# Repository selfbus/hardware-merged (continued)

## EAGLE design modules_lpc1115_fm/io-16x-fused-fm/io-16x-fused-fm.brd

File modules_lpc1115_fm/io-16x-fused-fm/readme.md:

<h1>Module with 16 fused IOs (flush mount) with I2C and SPI</h1>

The unversioned *.sch and *.brd files are the development files. 
Once a new version is released, a corresponding copy of the files with the release version appended to the file name are provided. 

Project documentation: https://selfbus.org/wiki/devices/inputs/82-multifunktions-io-modul-16x-fused-io-spi-i2c-serial</br>
Forum discussions: https://selfbus.org/forum/app.php/tag/Eingangsmodul

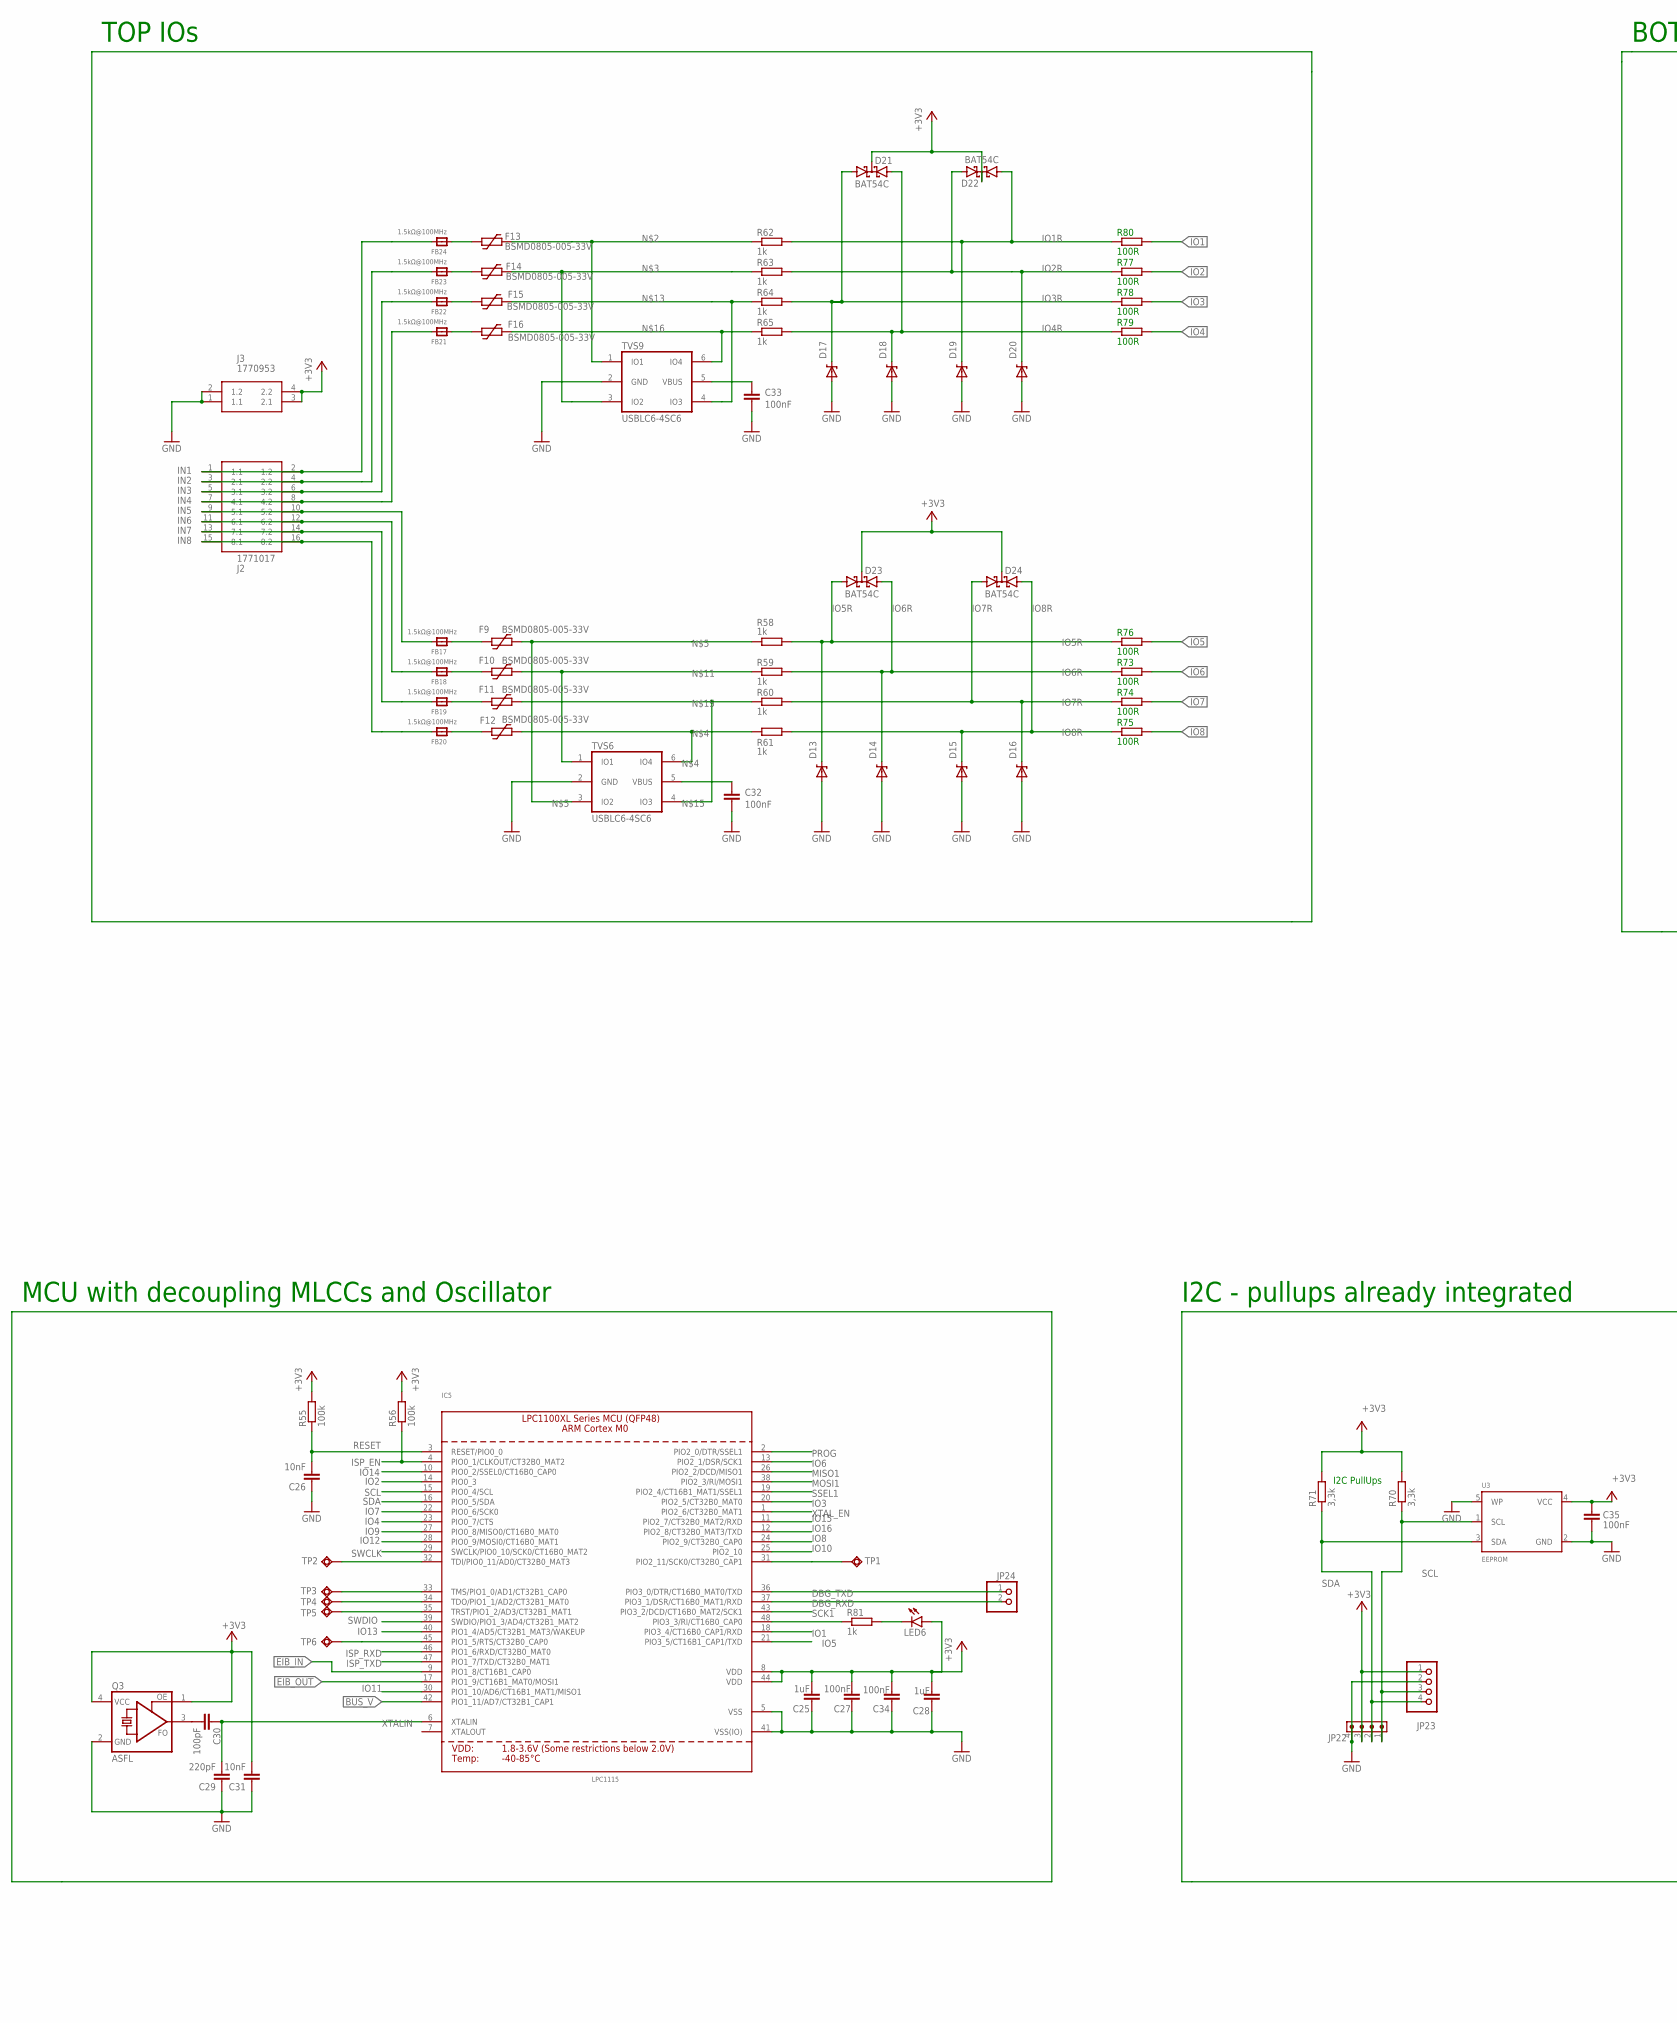
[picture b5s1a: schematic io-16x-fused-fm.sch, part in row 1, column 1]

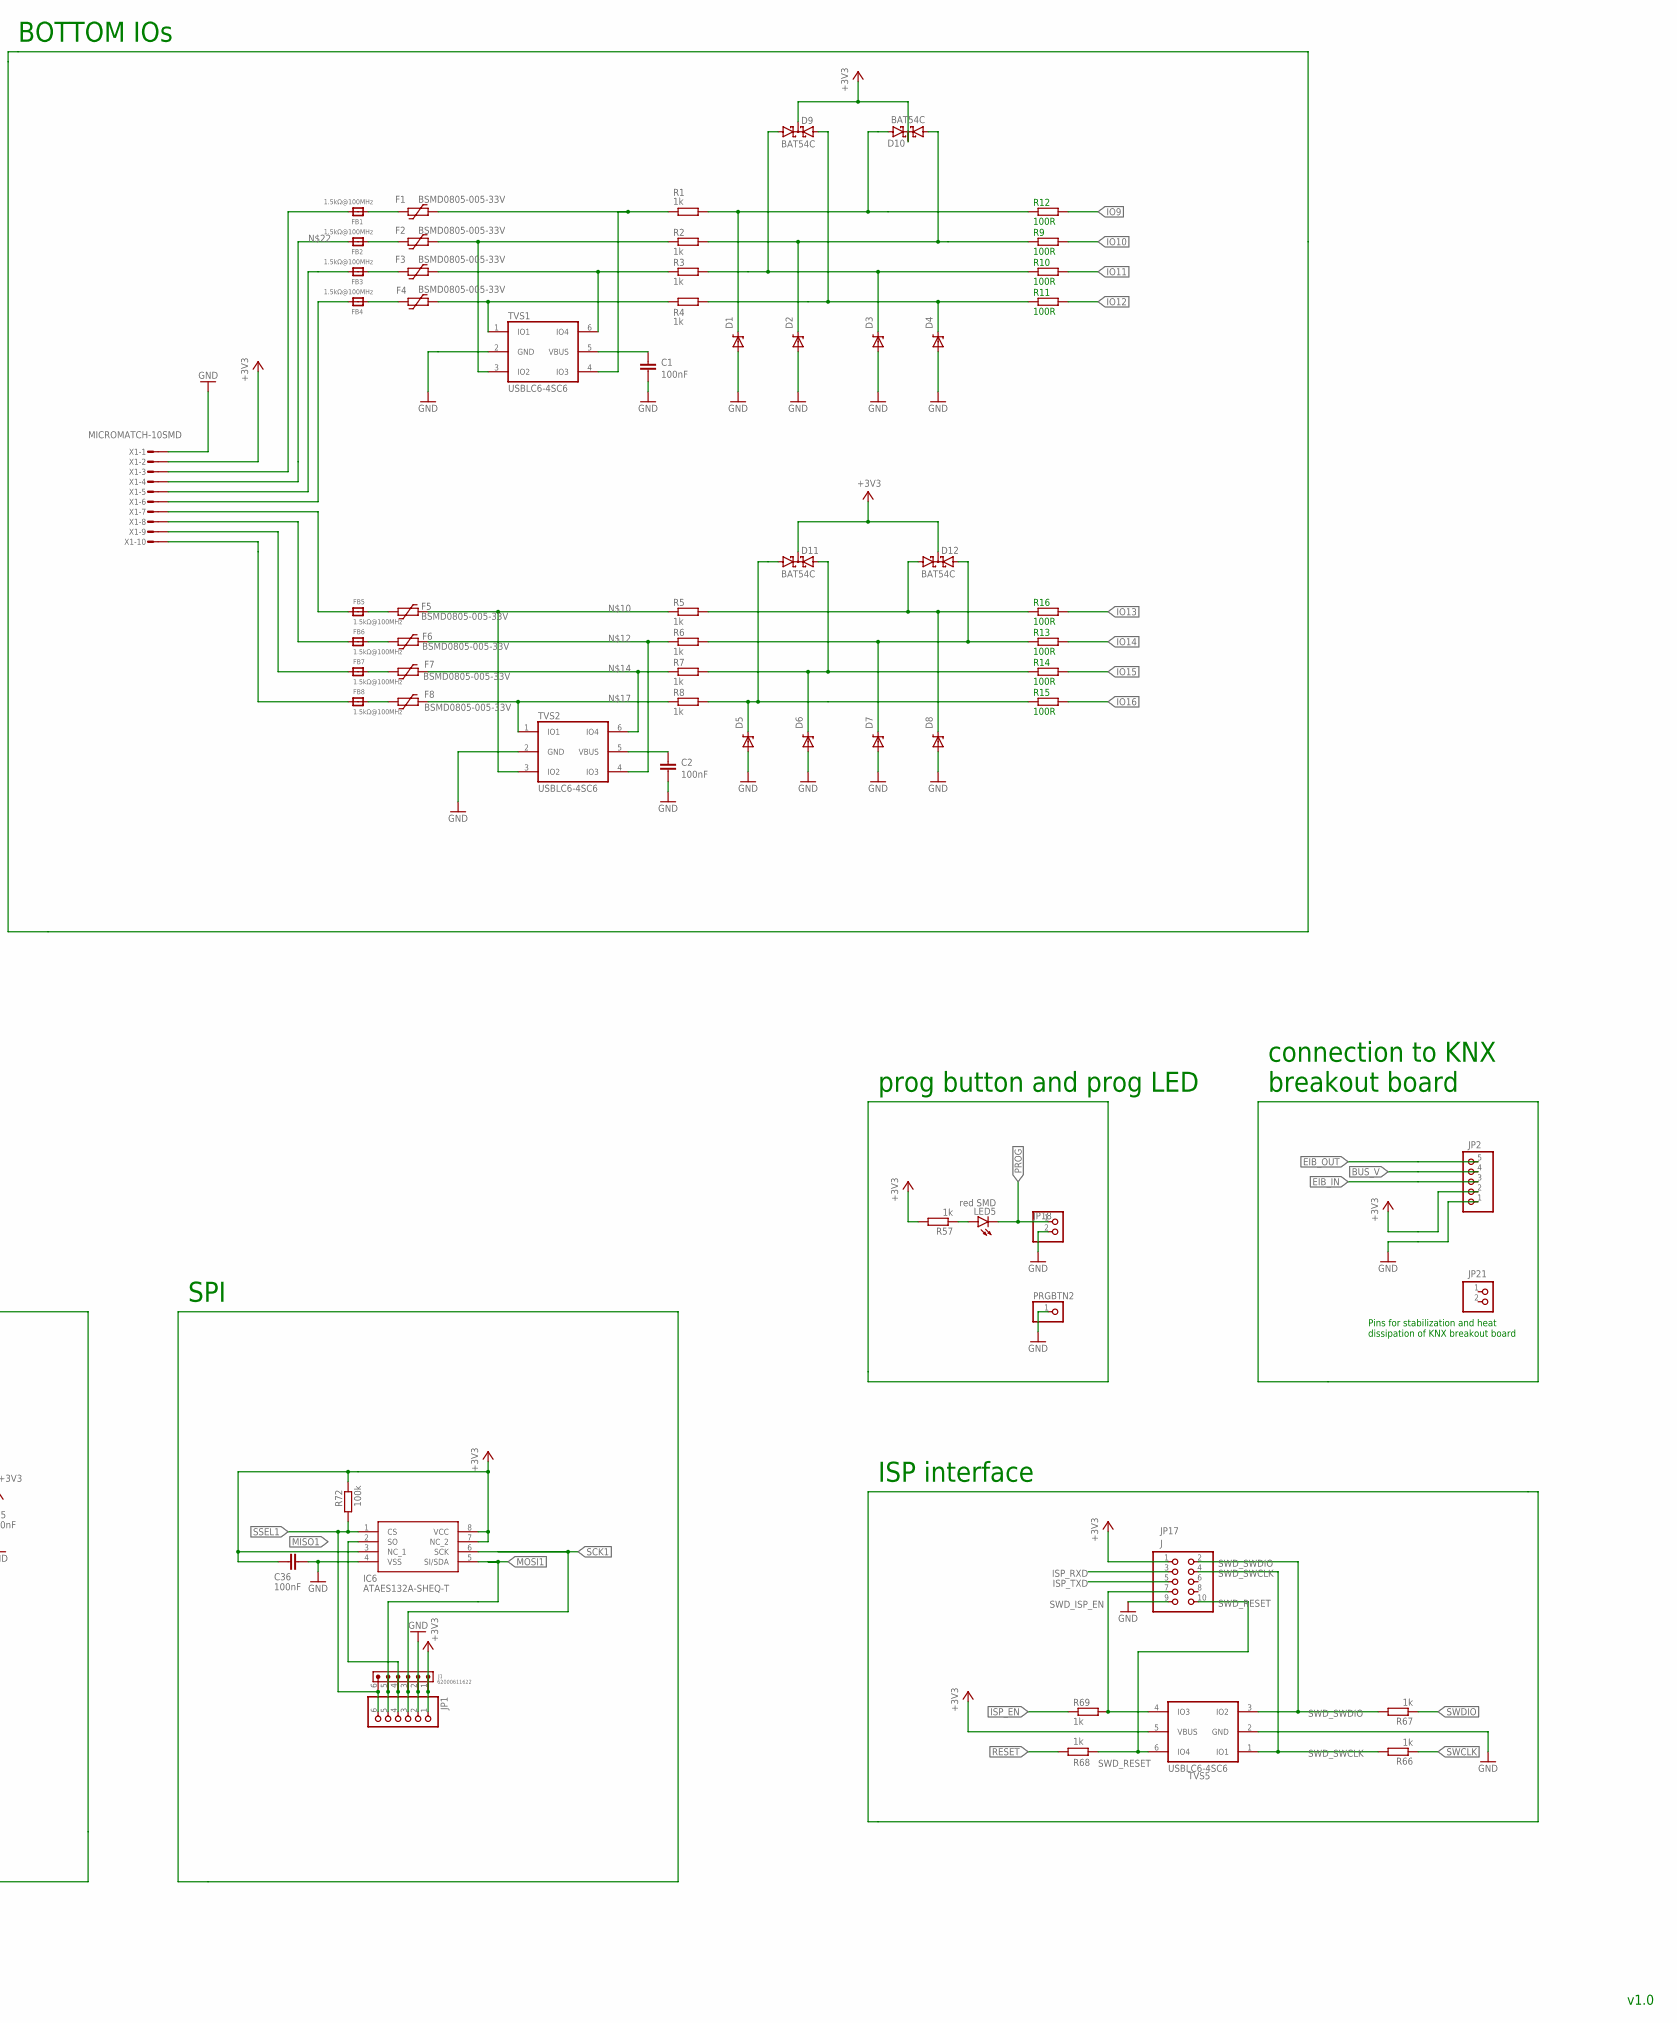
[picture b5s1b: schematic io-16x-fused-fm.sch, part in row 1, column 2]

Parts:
C1, C2, C27, C32, C33, C34, C35, C36: 100nF; C0805
C25, C28: 1uF; C0805
C26, C31: 10nF; C0805
C29: 220pF; C0805
C30: 100pF; C0805
D1, D2, D3, D4, D5, D6, D7, D8, D13, D14, D15, D16, D17, D18, D19, D20: DDZ9684; SOD-123
D9, D10, D11, D12, D21, D22, D23, D24: BAT54C; SOT23
F1, F2, F3, F4, F5, F6, F7, F8, F9, F10, F11, F12, F13, F14, F15, F16: BSMD0805-005-33V; 0805L
FB1, FB2, FB3, FB4, FB5, FB6, FB7, FB8, FB17, FB18, FB19, FB20, FB21, FB22, FB23, FB24: 1.5kΩ@100MHz; FERR_0805MP
IC5: LPC1115; LQFP48
IC6: ATAES132A-SHEQ-T; SOIC127P600X175-8N
J1: 62000611622
J2: 1771017
J3: 1770953
JP1: PINHD-1X06_2.54-S; 1X06-S
JP2: PINHD-1X5; 1X05
JP17: J; 2X05M
JP18, JP21, JP24: PINHD-1X2; 1X02
JP22: 62000411622
JP23: PINHD-1X4; 1X04
LED5: red SMD; CHIPLED_0805
LED6: LEDCHIPLED_0805; CHIPLED_0805
PRGBTN2: PINHD-1X1; 1X01
Q3: ASFL; ASF
R1, R2, R3, R4, R5, R6, R7, R8, R57, R58, R59, R60, R61, R62, R63, R64, R65, R66, R67, R68, R69, R81: 1k; R0805
R9, R10, R11, R12, R13, R14, R15, R16, R73, R74, R75, R76, R77, R78, R79, R80: 100R; R0805
R55, R56, R72: 100k; R0805
R70, R71: 3,3k; R0805
TP1, TP2, TP3, TP4, TP5, TP6: TPSQTP08R; TP08R
TVS1, TVS2, TVS5, TVS6, TVS9: USBLC6-4SC6; SOT-23-6L
U3: EEPROM; SOT23-5
X1: MICROMATCH-10SMD

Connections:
+3V3: C25.2, C27.2, C28.2, C31.2, C34.2, C35.1, C36.1, D9.3 (CC), D10.3 (CC), D11.3 (CC), D12.3 (CC), D21.3 (CC), D22.3 (CC), D23.3 (CC), D24.3 (CC), IC5.8 (VDD), IC5.44 (VDD), IC6.3 (NC_1), IC6.7 (NC_2), IC6.8 (VCC), J1.1, J3.3 (2.1), J3.4 (2.2), JP1.1, JP2.2, JP17.1, JP22.3, JP23.1, LED6.A, Q3.1 (OE), Q3.4 (VCC), R55.2, R56.2, R57.2, R70.2, R71.2, R72.2, TVS5.5 (VBUS), U3.4 (VCC), X1.2
BUS_V: IC5.42 (PIO1_11/AD7/CT32B1_CAP1), JP2.4
DBG_RXD: IC5.37 (PIO3_1/DSR/CT16B0_MAT1/RXD), JP24.2
DBG_TXD: IC5.36 (PIO3_0/DTR/CT16B0_MAT0/TXD), JP24.1
EIB_IN: IC5.9 (PIO1_8/CT16B1_CAP0), JP2.3
EIB_OUT: IC5.17 (PIO1_9/CT16B1_MAT0/MOSI1), JP2.5
GND: C1.1, C2.1, C25.1, C26.1, C27.1, C28.1, C29.1, C31.1, C32.1, C33.1, C34.1, C35.2, C36.2, D1.A, D2.A, D3.A, D4.A, D5.A, D6.A, D7.A, D8.A, D13.A, D14.A, D15.A, D16.A, D17.A, D18.A, D19.A, D20.A, IC5.5 (VSS), IC5.41 (VSS(IO)), IC6.4 (VSS), J1.2, J3.1 (1.1), J3.2 (1.2), JP1.2, JP2.1, JP17.9, JP18.2, JP22.4, JP23.2, PRGBTN2.1, Q3.2 (GND), TVS1.2 (GND), TVS2.2 (GND), TVS5.2 (GND), TVS6.2 (GND), TVS9.2 (GND), U3.2 (GND), U3.5 (WP), X1.1
IN1: FB24.2, J2.1 (1.1), J2.2 (1.2)
IN2: FB23.2, J2.3 (2.1), J2.4 (2.2)
IN3: FB22.2, J2.5 (3.1), J2.6 (3.2)
IN4: FB21.2, J2.7 (4.1), J2.8 (4.2)
IN5: FB17.2, J2.9 (5.1), J2.10 (5.2)
IN6: FB18.2, J2.11 (6.1), J2.12 (6.2)
IN7: FB19.2, J2.13 (7.1), J2.14 (7.2)
IN8: FB20.2, J2.15 (8.1), J2.16 (8.2)
IO1: IC5.18 (PIO3_4/CT16B0_CAP1/RXD), R80.2
IO1R: D19.C, D22.1 (A1), R62.2, R80.1
IO2: IC5.14 (PIO0_3), R77.2
IO2R: D20.C, D22.2 (A2), R63.2, R77.1
IO3: IC5.20 (PIO2_5/CT32B0_MAT0), R78.2
IO3R: D17.C, D21.1 (A1), R64.2, R78.1
IO4: IC5.23 (PIO0_7/CTS), R79.2
IO4R: D18.C, D21.2 (A2), R65.2, R79.1
IO5: IC5.21 (PIO3_5/CT16B1_CAP1/TXD), R76.2
IO5R: D13.C, D23.1 (A1), R58.2, R76.1
IO6: IC5.13 (PIO2_1/DSR/SCK1), R73.2
IO6R: D14.C, D23.2 (A2), R59.2, R73.1
IO7: IC5.22 (PIO0_6/SCK0), R74.2
IO7R: D16.C, D24.1 (A1), R60.2, R74.1
IO8: IC5.24 (PIO2_9/CT32B0_CAP0), R75.2
IO8R: D15.C, D24.2 (A2), R61.2, R75.1
IO9: IC5.27 (PIO0_8/MISO0/CT16B0_MAT0), R12.2
IO10: IC5.25 (PIO2_10), R9.2
IO11: IC5.30 (PIO1_10/AD6/CT16B1_MAT1/MISO1), R10.2
IO12: IC5.28 (PIO0_9/MOSI0/CT16B0_MAT1), R11.2
IO13: IC5.40 (PIO1_4/AD5/CT32B1_MAT3/WAKEUP), R16.2
IO14: IC5.10 (PIO0_2/SSEL0/CT16B0_CAP0), R13.2
IO15: IC5.11 (PIO2_7/CT32B0_MAT2/RXD), R14.2
IO16: IC5.12 (PIO2_8/CT32B0_MAT3/TXD), R15.2
ISP_EN: IC5.4 (PIO0_1/CLKOUT/CT32B0_MAT2), R56.1, R69.1
ISP_RXD: IC5.46 (PIO1_6/RXD/CT32B0_MAT0), JP17.3
ISP_TXD: IC5.47 (PIO1_7/TXD/CT32B0_MAT1), JP17.5
MISO1: IC5.26 (PIO2_2/DCD/MISO1), IC6.2 (SO), J1.4, JP1.4
MOSI1: IC5.38 (PIO2_3/RI/MOSI1), IC6.5 (SI/SDA), J1.5, JP1.5
unnamed: C30.2, Q3.3 (FO)
unnamed: F13.2, R62.1, TVS9.1 (IO1)
unnamed: F14.2, R63.1, TVS9.3 (IO2)
unnamed: F12.2, R61.1, TVS6.6 (IO4)
unnamed: F9.2, R58.1, TVS6.3 (IO2)
unnamed: F5.1, FB5.2
unnamed: F6.1, FB6.2
unnamed: F7.1, FB7.2
unnamed: F8.1, FB8.2
unnamed: F5.2, R5.1, TVS2.3 (IO2)
unnamed: F10.2, R59.1, TVS6.1 (IO1)
unnamed: F6.2, R6.1, TVS2.4 (IO3)
unnamed: F15.2, R64.1, TVS9.4 (IO3)
unnamed: F7.2, R7.1, TVS2.6 (IO4)
unnamed: F11.2, R60.1, TVS6.4 (IO3)
unnamed: F16.2, R65.1, TVS9.6 (IO4)
unnamed: F8.2, R8.1, TVS2.1 (IO1)
unnamed: D8.C, D12.1 (A1), R5.2, R16.1
unnamed: D7.C, D12.2 (A2), R6.2, R13.1
unnamed: IC5.45 (PIO1_5/RTS/CT32B0_CAP0), TP6.TP
unnamed: FB1.2, X1.3
unnamed: FB2.2, X1.4
unnamed: FB3.2, X1.5
unnamed: FB4.2, X1.6
unnamed: FB5.1, X1.7
unnamed: LED5.A, R57.1
unnamed: IC5.32 (TDI/PIO0_11/AD0/CT32B0_MAT3), TP2.TP
unnamed: C32.2, TVS6.5 (VBUS)
unnamed: C33.2, TVS9.5 (VBUS)
unnamed: F11.1, FB19.1
unnamed: F12.1, FB20.1
unnamed: F10.1, FB18.1
unnamed: F9.1, FB17.1
unnamed: F16.1, FB21.1
unnamed: F15.1, FB22.1
unnamed: F13.1, FB24.1
unnamed: F14.1, FB23.1
unnamed: LED6.C, R81.2
unnamed: IC5.48 (PIO3_3/RI/CT16B0_CAP0), R81.1
unnamed: FB6.1, X1.8
unnamed: FB7.1, X1.9
unnamed: FB8.1, X1.10
unnamed: D6.C, D11.2 (A2), R7.2, R14.1
unnamed: D5.C, D11.1 (A1), R8.2, R15.1
unnamed: C1.2, TVS1.5 (VBUS)
unnamed: IC5.33 (TMS/PIO1_0/AD1/CT32B1_CAP0), TP3.TP
unnamed: F1.1, FB1.1
unnamed: F2.1, FB2.1
unnamed: F3.1, FB3.1
unnamed: F4.1, FB4.1
unnamed: F4.2, R4.1, TVS1.1 (IO1)
unnamed: F3.2, R3.1, TVS1.6 (IO4)
unnamed: F2.2, R2.1, TVS1.3 (IO2)
unnamed: F1.2, R1.1, TVS1.4 (IO3)
unnamed: D1.C, D10.2 (A2), R1.2, R12.1
unnamed: D2.C, D10.1 (A1), R2.2, R9.1
unnamed: D3.C, D9.1 (A1), R3.2, R10.1
unnamed: D4.C, D9.2 (A2), R4.2, R11.1
unnamed: C2.2, TVS2.5 (VBUS)
unnamed: IC5.34 (TDO/PIO1_1/AD2/CT32B1_MAT0), TP4.TP
unnamed: IC5.35 (TRST/PIO1_2/AD3/CT32B1_MAT1), TP5.TP
unnamed: IC5.31 (PIO2_11/SCK0/CT32B0_CAP1), TP1.TP
PROG: IC5.2 (PIO2_0/DTR/SSEL1), JP18.1, LED5.C
RESET: C26.2, IC5.3 (RESET/PIO0_0), R55.1, R68.2
SCK1: IC5.43 (PIO3_2/DCD/CT16B0_MAT2/SCK1), IC6.6 (SCK), J1.3, JP1.3
SCL: IC5.15 (PIO0_4/SCL), JP22.1, JP23.3, R70.1, U3.1 (SCL)
SDA: IC5.16 (PIO0_5/SDA), JP22.2, JP23.4, R71.1, U3.3 (SDA)
SSEL1: IC5.19 (PIO2_4/CT16B1_MAT1/SSEL1), IC6.1 (CS), J1.6, JP1.6, R72.1
SWCLK: IC5.29 (SWCLK/PIO0_10/SCK0/CT16B0_MAT2), R66.1
SWDIO: IC5.39 (SWDIO/PIO1_3/AD4/CT32B1_MAT2), R67.1
SWD_ISP_EN: JP17.7, R69.2, TVS5.4 (IO3)
SWD_RESET: JP17.10, R68.1, TVS5.6 (IO4)
SWD_SWCLK: JP17.4, R66.2, TVS5.1 (IO1)
SWD_SWDIO: JP17.2, R67.2, TVS5.3 (IO2)
XTALIN: C29.2, C30.1, IC5.6 (XTALIN)
XTAL_EN: IC5.1 (PIO2_6/CT32B0_MAT1)

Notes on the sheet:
I2C PullUps
Pins for stabilization and heat dissipation of KNX breakout board
MCU with decoupling MLCCs and Oscillator
TOP IOs
BOTTOM IOs
I2C - pullups already integrated
SPI
prog button and prog LED
connection to KNX breakout board
ISP interface
v1.0

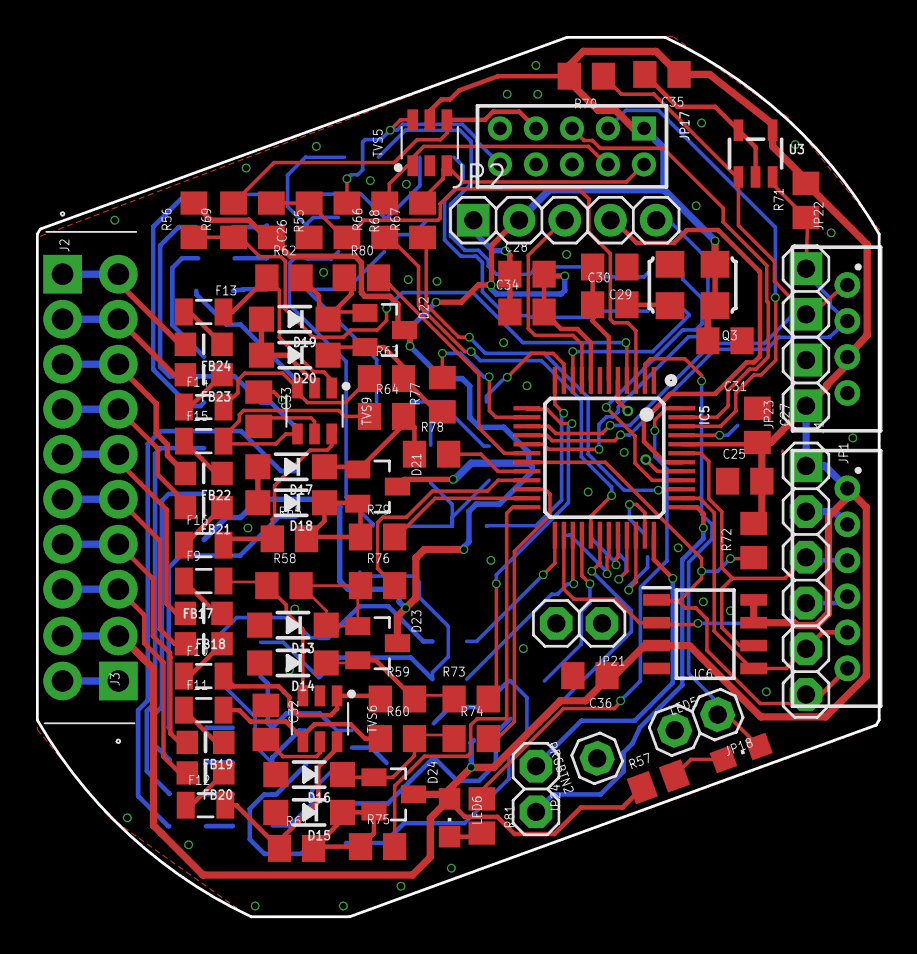
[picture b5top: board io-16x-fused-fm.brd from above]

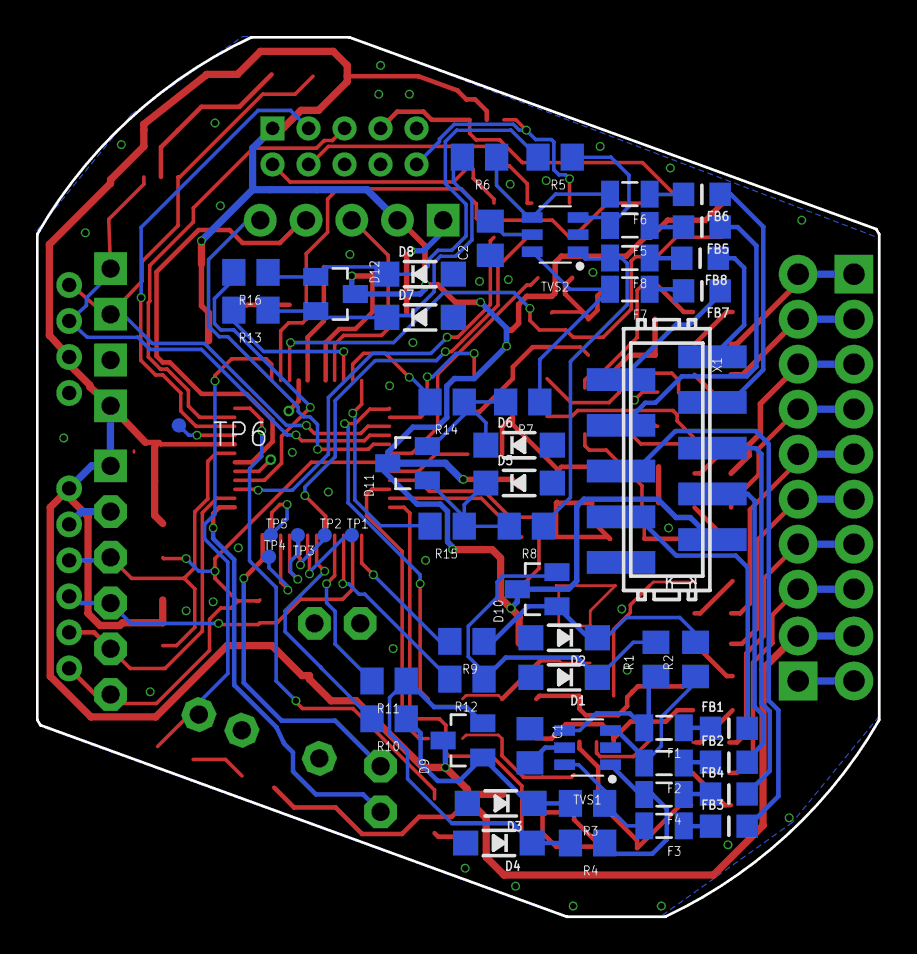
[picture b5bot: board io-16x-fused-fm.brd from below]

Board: 2 copper layers, 46.8 x 48.9 mm, 143 parts (55 on the bottom side), 119 nets.
